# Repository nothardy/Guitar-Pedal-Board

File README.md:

# Guitar-Pedal-Board

Guitar Pedal Board in C++, implemented on MATLAB and Arduino due.

# How it works?

- First code is a MATLAB script which samples a clean guitar .wav file and plots its time function and frequency spectrum. Then each scrip section implements a filter that mimics a guitar pedal effect, such as: flangers, overdrive, low-pass and high-pass; also plotting the result time function and frequency spectrum.

- Second code goes by the same idea as the first one, but adapted for an Arduino Due board in C++. For this arduino board, a shield board was designed and solder so that the user can adjust volume and connect a guitar and also an amplifier. Two versions of this code were uploaded, first one including a led display; the second one, a more clean and newer version already debugged and without the display.

All of these guitar effects were calculated using the discrete Fourier Transform and Sampling Theory, learnt in a Digital Signal Processing course at Uncoma. Each effect is represented by a impulse response that is applyed to the input signal received at the Arduino.

# Can I try it at home?

Sure! Although, you may need to implement/solder your own shield board. Kinda messy huh? Well, you still can try the MATLAB version. It runs on MATLAB R2016a and higher!

- First step is to have MATLAB installed and download .m script and .wav file all together in a same folder. Then run first section of the code by stepping into it and pressing Ctrl + Enter. Math plot windows will show and you will hear wav file playing, it's a clean guitar sample.

- Second step is to choose any filter, step into it and run Ctrl + Enter, you will hear the same guitar sample but with effects now!

You can see my demo <a href="https://www.linkedin.com/posts/julian-pinel_c-matlab-arduino-activity-6826684093904764928-YmtJ" target="_blank" ref="noreferred">here </a>

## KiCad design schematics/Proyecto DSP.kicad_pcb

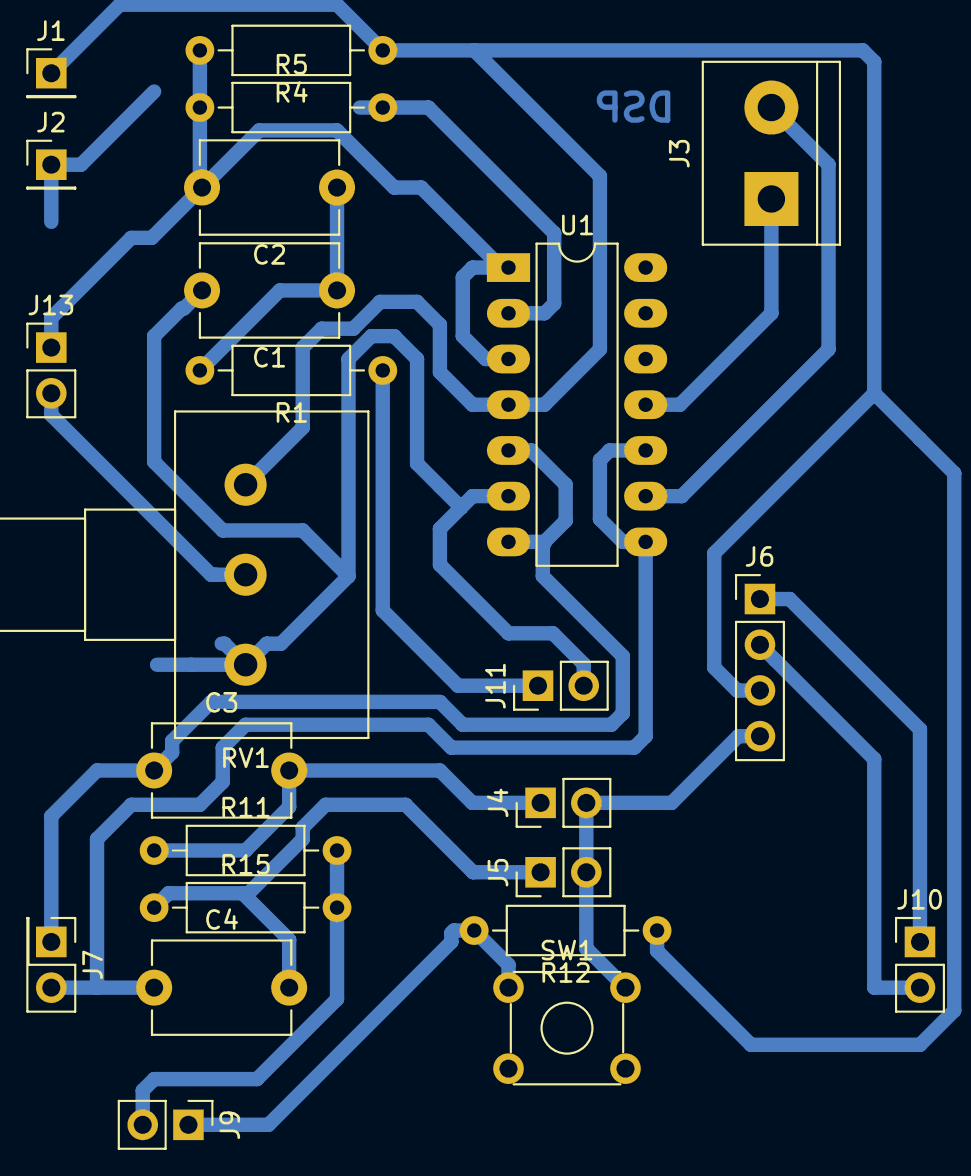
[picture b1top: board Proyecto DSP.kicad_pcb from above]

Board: 2 copper layers, 24 parts (0 on the bottom side), 14 nets.

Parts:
C1: 10n; C_Disc_D7.5mm_W5.0mm_P7.50mm
C2: 100n; C_Disc_D7.5mm_W5.0mm_P7.50mm
C3, C4: 33n; C_Disc_D7.5mm_W5.0mm_P7.50mm
J1: 3.3v; PinHeader_1x01_P2.54mm_Vertical
J2: GND; PinHeader_1x01_P2.54mm_Vertical
J3: GND -3.3v; TerminalBlock_bornier-2_P5.08mm
J4: DAC0; PinHeader_1x02_P2.54mm_Vertical
J5: DAC1; PinHeader_1x02_P2.54mm_Vertical
J6: OLED; PinHeader_1x04_P2.54mm_Vertical
J7: DAC0 DAC1; PinHeader_2x01_P2.54mm_Vertical
J9: Con boton; PinHeader_1x02_P2.54mm_Vertical
J10: SDA SCL; PinHeader_1x02_P2.54mm_Vertical
J11: Audio IN; PinHeader_1x02_P2.54mm_Vertical
J13: A0 A1; PinHeader_1x02_P2.54mm_Vertical
R1: 680; R_Axial_DIN0207_L6.3mm_D2.5mm_P10.16mm_Horizontal
R4, R5: 160k; R_Axial_DIN0207_L6.3mm_D2.5mm_P10.16mm_Horizontal
R11, R15: 470k; R_Axial_DIN0207_L6.3mm_D2.5mm_P10.16mm_Horizontal
R12: R; R_Axial_DIN0207_L6.3mm_D2.5mm_P10.16mm_Horizontal
RV1: R_POT; Potentiometer_Alps_RK163_Single_Horizontal
SW1: SW_Push_Dual; SW_TH_Tactile_Omron_B3F-10xx
U1: LM324; DIP-14_W7.62mm_LongPads

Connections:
52: J9.1, R12.2, SW1.1
+3V3: J1.1, J6.3, R4.1, R12.1, RV1.1, U1.4
-3V3: J3.1, U1.11
A0: C2.2, J13.1, R4.2, R5.1, U1.1, U1.3
A1: J13.2, RV1.2
DAC0: C3.1, J7.1, U1.5, U1.7
DAC1: C4.1, J7.2, U1.8, U1.10
GND: C1.2, J2.1, J3.2, J4.2, J5.2, J6.4, J9.2, J11.2, R5.2, R11.2, R15.2, RV1.3, SW1.2, U1.2, U1.6, U1.9
unnamed: C1.1, C2.1, R1.2
SCL: J6.2, J10.2
SDA: J6.1, J10.1
Vin: J11.1, R1.1
Vout0: C3.2, J4.1, R11.1
Vout1: C4.2, J5.1, R15.1

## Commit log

2021-07-27 first commit of dsp files
2021-07-27 modified path search on matlab file
2021-07-27 final matlab push
2021-07-27 added schematics
2021-07-29 readme instructions
2021-07-29 added yt video
2021-07-30 link fix
